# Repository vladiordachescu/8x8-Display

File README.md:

# 8x8 Display with Attiny85 microcontroller

https://github.com/vladiordachescu/8x8-display-attiny85/assets/73362552/db192aa6-c74f-46c0-92d8-602dc996fab3

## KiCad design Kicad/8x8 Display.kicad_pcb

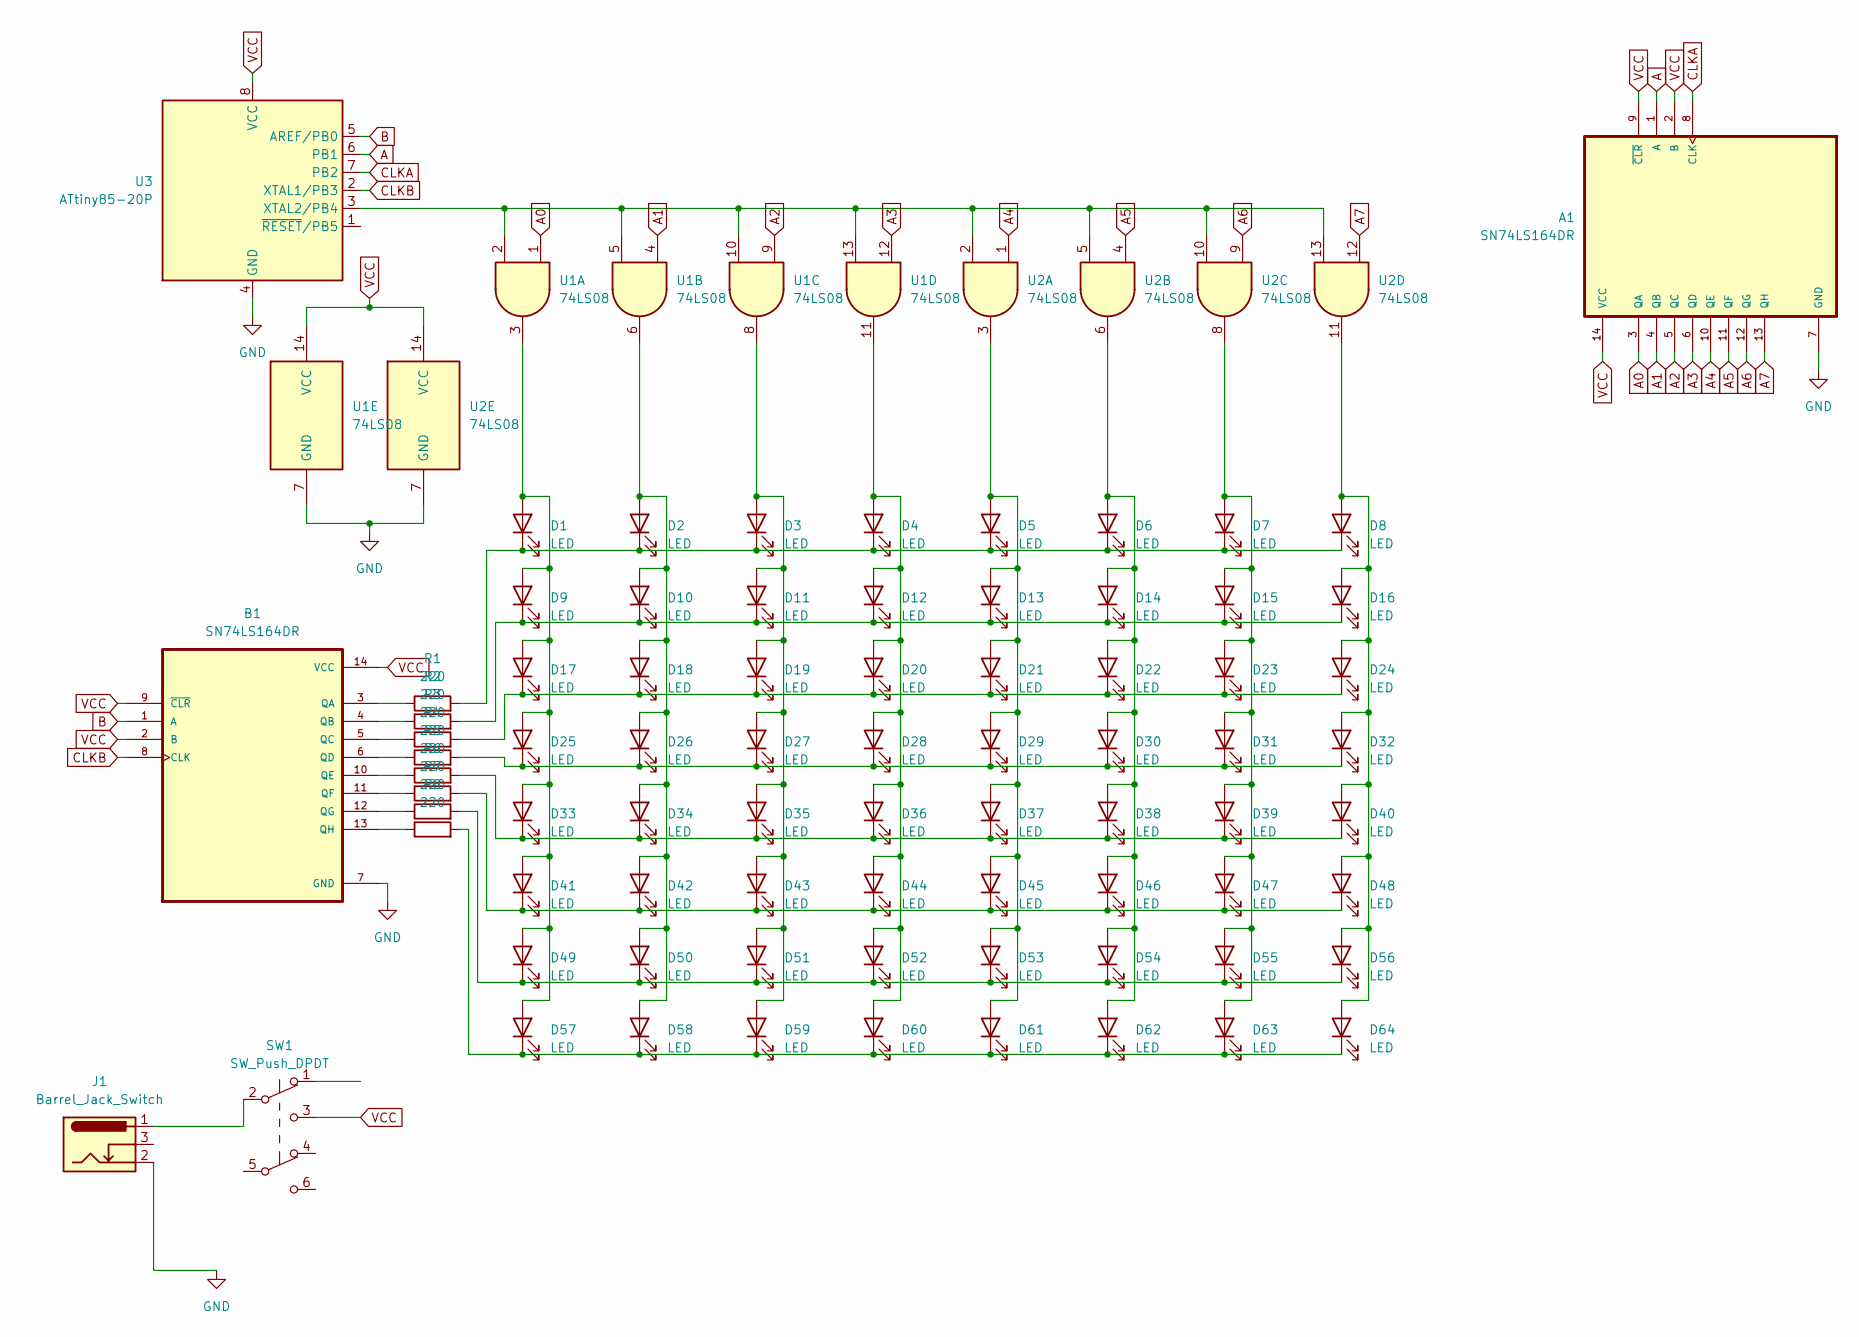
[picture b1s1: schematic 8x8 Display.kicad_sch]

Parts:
A1: SN74LS164DR; SOIC127P600X175-14N
B1: SN74LS164DR; SOIC127P600X175-14N
D1, D2, D3, D4, D5, D6, D7, D8, D9, D10, D11, D12, D13, D14, D15, D16, D17, D18, D19, D20, D21, D22, D23, D24, D25, D26, D27, D28, D29, D30, D31, D32, D33, D34, D35, D36, D37, D38, D39, D40, D41, D42, D43, D44, D45, D46, D47, D48, D49, D50, D51, D52, D53, D54, D55, D56, D57, D58, D59, D60, D61, D62, D63, D64: LED; LED_0805_2012Metric
J1: Barrel_Jack_Switch; BarrelJack_Horizontal
R1, R2, R3, R4, R5, R6, R7, R8: 220; R_0805_2012Metric
SW1: SW_Push_DPDT; push_cu_6_pini
U1: 74LS08; SOIC127P600X175-14N
U2: 74LS08
U3: ATtiny85-20P; DIP-8_W7.62mm

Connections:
A: A1.1 (A), U3.6 (PB1)
A0: A1.3 (QA), U1.1
A1: A1.4 (QB), U1.4
A2: A1.5 (QC), U1.9
A3: A1.6 (QD), U1.12
A4: A1.10 (QE), U2.1
A5: A1.11 (QF), U2.4
A6: A1.12 (QG), U2.9
A7: A1.13 (QH), U2.12
B: B1.1 (A), U3.5 (AREF/PB0)
CLKA: A1.8 (CLK), U3.7 (PB2)
CLKB: B1.8 (CLK), U3.2 (XTAL1/PB3)
GND: A1.7 (GND), B1.7 (GND), J1.2, U1.7 (GND), U2.7 (GND), U3.4 (GND)
unnamed: B1.3 (QA), R1.1
unnamed: B1.4 (QB), R2.1
unnamed: B1.5 (QC), R3.1
unnamed: B1.6 (QD), R4.1
unnamed: B1.10 (QE), R5.1
unnamed: B1.11 (QF), R6.1
unnamed: B1.12 (QG), R7.1
unnamed: B1.13 (QH), R8.1
unnamed: D1.2 (A), D9.2 (A), D17.2 (A), D25.2 (A), D33.2 (A), D41.2 (A), D49.2 (A), D57.2 (A), U1.3
unnamed: D1.1 (K), D2.1 (K), D3.1 (K), D4.1 (K), D5.1 (K), D6.1 (K), D7.1 (K), D8.1 (K), R1.2
unnamed: D2.2 (A), D10.2 (A), D18.2 (A), D26.2 (A), D34.2 (A), D42.2 (A), D50.2 (A), D58.2 (A), U1.6
unnamed: D9.1 (K), D10.1 (K), D11.1 (K), D12.1 (K), D13.1 (K), D14.1 (K), D15.1 (K), D16.1 (K), R2.2
unnamed: D3.2 (A), D11.2 (A), D19.2 (A), D27.2 (A), D35.2 (A), D43.2 (A), D51.2 (A), D59.2 (A), U1.8
unnamed: D4.2 (A), D12.2 (A), D20.2 (A), D28.2 (A), D36.2 (A), D44.2 (A), D52.2 (A), D60.2 (A), U1.11
unnamed: D5.2 (A), D13.2 (A), D21.2 (A), D29.2 (A), D37.2 (A), D45.2 (A), D53.2 (A), D61.2 (A), U2.3
unnamed: D6.2 (A), D14.2 (A), D22.2 (A), D30.2 (A), D38.2 (A), D46.2 (A), D54.2 (A), D62.2 (A), U2.6
unnamed: D7.2 (A), D15.2 (A), D23.2 (A), D31.2 (A), D39.2 (A), D47.2 (A), D55.2 (A), D63.2 (A), U2.8
unnamed: D8.2 (A), D16.2 (A), D24.2 (A), D32.2 (A), D40.2 (A), D48.2 (A), D56.2 (A), D64.2 (A), U2.11
unnamed: D17.1 (K), D18.1 (K), D19.1 (K), D20.1 (K), D21.1 (K), D22.1 (K), D23.1 (K), D24.1 (K), R3.2
unnamed: D25.1 (K), D26.1 (K), D27.1 (K), D28.1 (K), D29.1 (K), D30.1 (K), D31.1 (K), D32.1 (K), R4.2
unnamed: D33.1 (K), D34.1 (K), D35.1 (K), D36.1 (K), D37.1 (K), D38.1 (K), D39.1 (K), D40.1 (K), R5.2
unnamed: D41.1 (K), D42.1 (K), D43.1 (K), D44.1 (K), D45.1 (K), D46.1 (K), D47.1 (K), D48.1 (K), R6.2
unnamed: D49.1 (K), D50.1 (K), D51.1 (K), D52.1 (K), D53.1 (K), D54.1 (K), D55.1 (K), D56.1 (K), R7.2
unnamed: D57.1 (K), D58.1 (K), D59.1 (K), D60.1 (K), D61.1 (K), D62.1 (K), D63.1 (K), D64.1 (K), R8.2
unnamed: J1.1, SW1.2 (B)
unnamed: U1.2, U1.5, U1.10, U1.13, U2.2, U2.5, U2.10, U2.13, U3.3 (XTAL2/PB4)
VCC: A1.2 (B), A1.9 (~CLR), A1.14 (VCC), B1.2 (B), B1.9 (~CLR), B1.14 (VCC), SW1.3 (C), U1.14 (VCC), U2.14 (VCC), U3.8 (VCC)

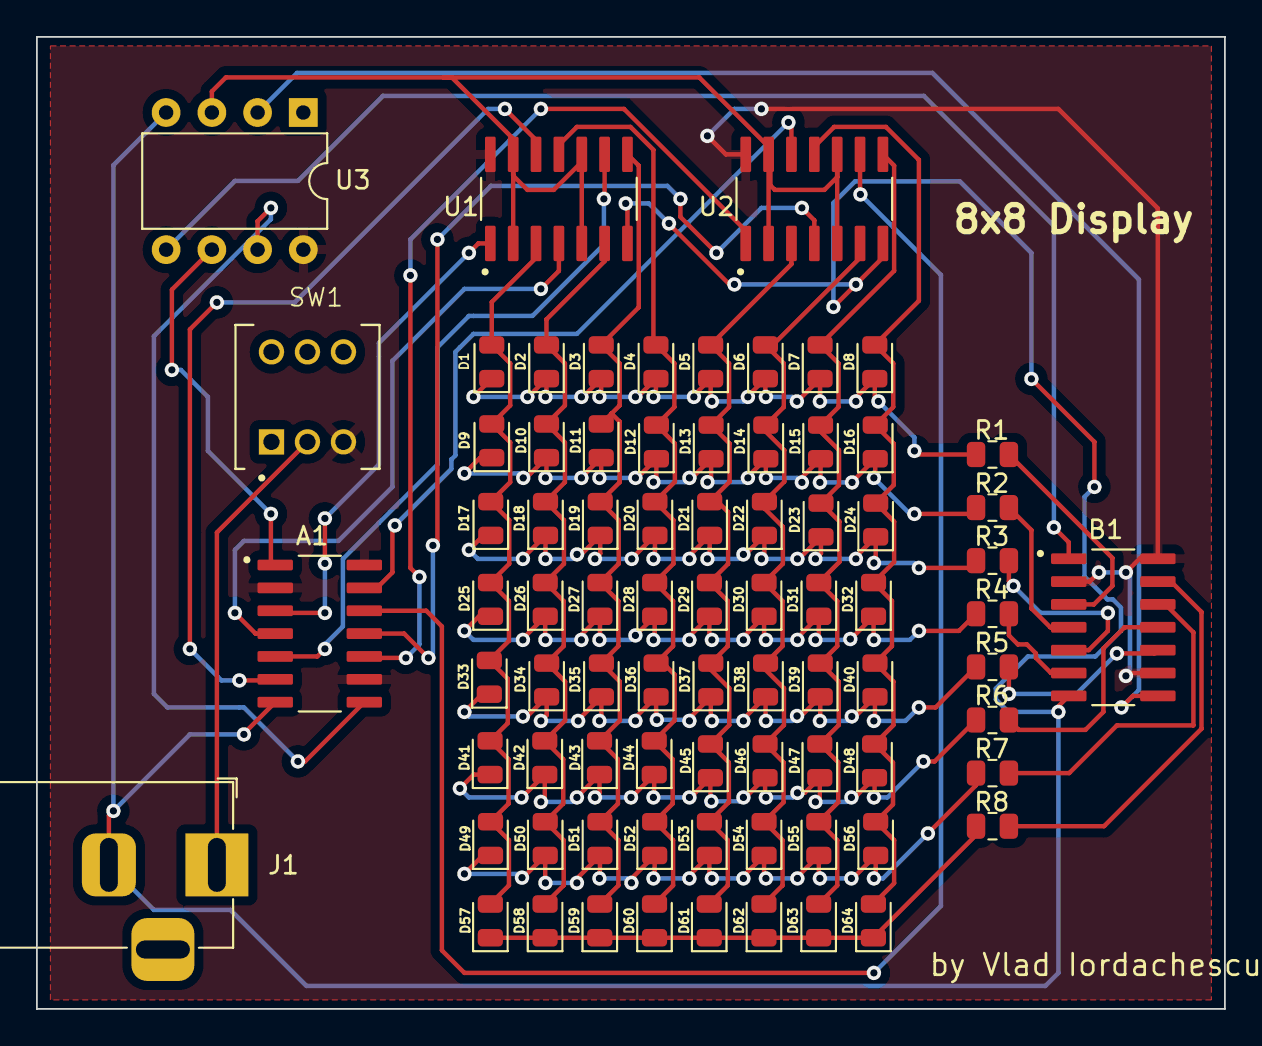
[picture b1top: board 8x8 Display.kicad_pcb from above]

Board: 2 copper layers, 66.0 x 54.0 mm, 79 parts (0 on the bottom side), 40 nets.

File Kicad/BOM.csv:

#,Reference,Qty,Value,Footprint,DNP
1,"A1, B1",2,SN74LS164DR,SN74LS164DR:SOIC127P600X175-14N,
2,"D1, D2, D3, D4, D5, D6, D7, D8, D9, D10, D11, D12, D13, D14, D15, D16, D17, D18, D19, D20, D21, D22, D23, D24, D25, D26, D27, D28, D29, D30, D31, D32, D33, D34, D35, D36, D37, D38, D39, D40, D41, D42, D43, D44, D45, D46, D47, D48, D49, D50, D51, D52, D53, D54, D55, D56, D57, D58, D59, D60, D61, D62, D63, D64",64,LED,LED_SMD:LED_0805_2012Metric,
3,J1,1,Barrel_Jack_Switch,Connector_BarrelJack:BarrelJack_Horizontal,
4,"R1, R2, R3, R4, R5, R6, R7, R8",8,220,Resistor_SMD:R_0805_2012Metric,
5,SW1,1,SW_Push_DPDT,Push_6pin:push_cu_6_pini,
6,"U1, U2",2,74LS08,SN74LS164DR:SOIC127P600X175-14N,
7,U3,1,ATtiny85-20P,Package_DIP:DIP-8_W7.62mm,

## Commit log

2024-02-14 Added sketch and hex files
2024-02-14 Create README.md
    Added README
2024-02-15 Added schematic and pcb files
2024-02-15 Added BOM
2024-02-15 Formatting BOM.csv
2024-02-16 Added comments to code
    Also renamed hex file to match the name of the ino file
